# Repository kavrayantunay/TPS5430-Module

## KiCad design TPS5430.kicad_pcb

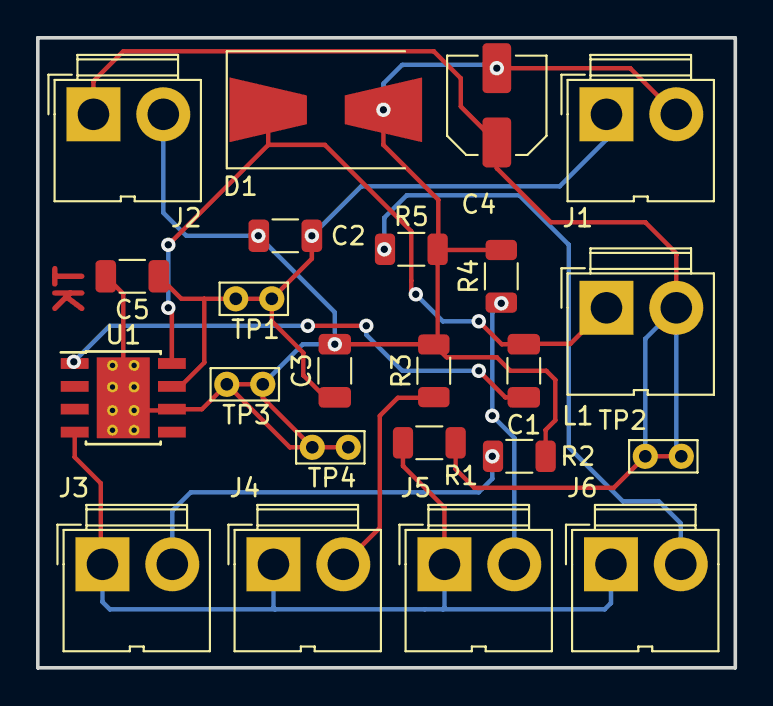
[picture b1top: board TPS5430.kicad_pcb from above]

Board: 2 copper layers, 38.8 x 35.0 mm, 23 parts (0 on the bottom side), 10 nets.

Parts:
C1: 10nF; C_1206_3216Metric
C2: 4.7uF; C_1206_3216Metric
C3, C5: 10uF; C_1206_3216Metric
C4: 220uF; C_Elec_5x5.4
D1: B340A; D_SMB-SMC_Universal_Handsoldering
J1, J2: klemens; JWT_A3963_1x02_P3.96mm_Vertical
J3: 5V; JWT_A3963_1x02_P3.96mm_Vertical
J4: 3.3V; JWT_A3963_1x02_P3.96mm_Vertical
J5: 2.5V; JWT_A3963_1x02_P3.96mm_Vertical
J6: 1.8V; JWT_A3963_1x02_P3.96mm_Vertical
L1: 22uH; JWT_A3963_1x02_P3.96mm_Vertical
R1: 10K; R_1206_3216Metric
R2: 3.24K; R_1206_3216Metric
R3: 5.9K; R_1206_3216Metric
R4: 9.53K; R_1206_3216Metric
R5: 21.5K; R_1206_3216Metric
TP1, TP2, TP3, TP4: TestPoint; TestPoint_Bridge_Pitch2.0mm_Drill0.7mm
U1: TPS5430DDA; TI_SO-PowerPAD-8_ThermalVias

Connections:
/PH: C1.2, D1.1 (K), L1.1, U1.8 (PH)
/VIN: C2.1, C3.1, C5.1, J1.1 (Vcc), TP1.1, U1.7 (VIN)
/VOUT: C4.1, J2.1 (Vcc), L1.2, R1.1, TP2.1
GND: C2.2, C3.2, C4.2, C5.2, D1.2 (A), J1.2 (GND), J2.2 (GND), R2.2, R3.2, R4.2, R5.2, TP3.1, TP4.1, U1.6 (GND), U1.9 (GNDPAD)
unnamed: C1.1, U1.1 (BOOT)
unnamed: J3.2 (GND), R2.1
unnamed: J4.2 (GND), R3.1
unnamed: J5.2 (GND), R4.1
unnamed: J6.2 (GND), R5.1
sense: J3.1 (Vcc), J4.1 (Vcc), J5.1 (Vcc), J6.1 (Vcc), R1.2, U1.4 (VSENSE)
